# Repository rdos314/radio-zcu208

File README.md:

<h3>Source tree</h3>
vivado - Vivado Verilog source<br>
vitis - Vitis platform and control software<br>
linux - Peta-linux source<br>

<h3>PetaLinux build</h3>
Ubuntu 22.04.5 must be used to build PetaLinux. Link: https://releases.ubuntu.com/jammy/<br><br>

Create a user "ubuntu" since full paths are used in the source.

Install the required software modules before installing PetaLinux:<br>
sudo apt-get install iproute2 gawk python3 python build-essential gcc git make net-tools libncurses5-dev tftpd zlib1g-dev libssl-dev flex bison libselinux1 gnupg wget git-core diffstat chrpath socat xterm autoconf libtool tar unzip texinfo<br><br>

The PetaLinux installer can be downloaded here: https://www.xilinx.com/support/download/index.html/content/xilinx/en/downloadNav/embedded-design-tools.html<br>
Download the "PetaLinux installer" and the "ZCU208 BSP" to /home/ubuntu<br><br>

Install PetaLinux like this:<br>
chmod 755 ./petalinux-v2025.1-final-installer.run<br>
./petalinux-v2025.1-final-installer.run --dir /home/ubuntu/petalinux --platform "arm aarch64"<br>

Source PetaLinux before running commands:<br>
source /home/ubuntu/petalinux/settings.sh<br><br>

Create the project:<br>
mkdir radio-zcu208<br>
cd radio-zcu208<br><br>

petalinux-create -t project -s zcu208-v2025.1.bsp -n linux<br>
cd linux<br><br>

petalinux-config --get-hw-description ../platform/export/platform/hw/sdt<br><br>

Subsystem Hardware Settings -→ Memory settings -→ Set Memory size to 0x70000000<br>
Subsystem Hardware Settings -→ Ethernet settings -→ Disable obtain IP address automatically<br>
Subsystem Hardware Settings -→ Ethernet settings -→ Set Static IP address to 192.168.1.90<br>
Subsystem Hardware Settings -→ Ethernet settings -→ Set Static IP gateway to 192.168.1.1<br>
Image Packaging Configuration  -→  Set Root file system type to EXT4 (SD/eMMC/SATA/USB)<br>

Exit menuconfig and save configuration settings.<br><br>

petalinux-config -c rootfs.<br>

Filesystem Packages -→ console -→ network -→ OpenSSH -→ set openssh-sftp-server to enabled<br>
Filesystem Packages -→ misc -→ set tcf-agent to enabled<br>
Filesystem Packages -→ misc -→ set apache2 to enabled<br><br>

Exit menuconfig and save configuration settings.<br><br>

petalinux-build<br>
petalinux-package boot --uboot --force<br>
petalinux-build --sdk<br>
petalinux-package sysroot<br><br>

Copy linux/images/linux/b31.bin to project roo<br>
Copy linux/images/linux/system.dtb to project root<br>
Copy linux/images/linux/u-boot.elf to project root<br>
Copy linux/images/linux/sdk/sysroots/cortexa72-cotexa53-amd-linux/usr/include to project platform/usr/include<br>
Copy linux/images/linux/sdk/sysroots/cortexa72-cotexa53-amd-linux/usr/lib to project platform/usr/lib<br><br>

cp linux/images/linux/image.ub /media/ubuntu/boot<br>
cp linux/images/linux/boot.scr /media/ubuntu/boot<br>
sudo dd if=linux/images/linux/rootfs.ext4 of=/dev/sdb2<br><br>

<h3>Embedded Vitis</h3>

Embedded Vitis and Vivado can be installed either on Windows or on Linux. Link: https://www.xilinx.com/support/download/index.html/content/xilinx/en/downloadNav/vitis.html<br><br>

For Linux, download and install to /home/user/xilinx and then install the libs like this:<br>
cd /home/user/xilinx/2025.1/Vitis/scripts<br>
sudo ./installLibs.sh<br><br>

<h3>XRT and ZOCL</h3>

https://adaptivesupport.amd.com/s/article/1138667?language=en_US

<h3>Antennas and preamplifiers</h3>

Isolator: https://www.herostechnology.co.uk/pages/RF_Galvanic_Isolators.html                            3 MHz - 2.5 GHz<br>
LNA: https://www.pasternack.com/1.5-db-1.3-ghz-low-noise-amplifier-35-db-gain-sma-pe15a1054-p.aspx      10MHz - 1.3GHz, 35dB, 1.5 NF<br>
LNA: https://www.pasternack.com/1.7-db-550-mhz-low-noise-amplifier-29.7-db-gain-sma-pe15a1044-p.aspx    10MHz - 550 MHz, 30dB, 1.7 NF<br><br>

<h3>Example design</h3>

doc: https://docs.amd.com/r/en-US/ug1309-rf-data-converter-interface<br>
source: https://account.amd.com/en/forms/downloads/design-license-xef.html?filename=RF_Analyzer_2024_2.zip<br><br>

doc: https://www.xilinx.com/publications/products/board-kits/zcu208-dds-ila-2020p2.pdf<br>
source: https://account.amd.com/en/forms/downloads/design-license-xef.html?filename=ZCU208_dds_ila_2020p2.zip<br>

<h3>Important links</h3>
https://www.amd.com/en/products/adaptive-socs-and-fpgas/evaluation-boards/zcu208.html<br>
https://xilinx-wiki.atlassian.net/wiki/spaces/A/pages/18841823/Booting+via+Serial+ATA+SATA+on+ZCU102+Evaluation+Platform<br>
https://adaptivesupport.amd.com/s/article/000037805?language=en_US<br>
https://xilinx-wiki.atlassian.net/wiki/spaces/A/pages/18842475/PetaLinux+Yocto+Tips#PetaLinuxYoctoTips-HowtoAutoRunApplicationatStartup<br>
https://docs.amd.com/r/en-US/Vitis-Tutorials-Embedded-Software<br>
https://docs.amd.com/r/en-US/ug1209-embedded-design-tutorial/Tutorial-Design-Files<br>
https://numato.com/kb/styx-partitioning-sd-card-for-petalinux/<br>
https://adaptivesupport.amd.com/s/article/1192842?language=en_US<br>
https://github.com/Xilinx/embeddedsw/blob/master/XilinxProcessorIPLib/drivers/rfdc/examples/xrfdc_mts_example.c<br>
https://docs.amd.com/r/en-US/pg269-rf-data-converter/MTS-Sequencing<br>
https://docs.amd.com/r/en-US/ug835-vivado-tcl-commands/<br>
https://github.com/Xilinx/embeddedsw/tree/master/XilinxProcessorIPLib/drivers/board_common/src/rfclk<br>
https://layers.openembedded.org/layerindex/branch/master/layers/<br>
https://www.analog.com/en/products/adl5569.html<br>
https://ez.analog.com/rf/f/q-a/115814/adl5569-single-ended-input<br>

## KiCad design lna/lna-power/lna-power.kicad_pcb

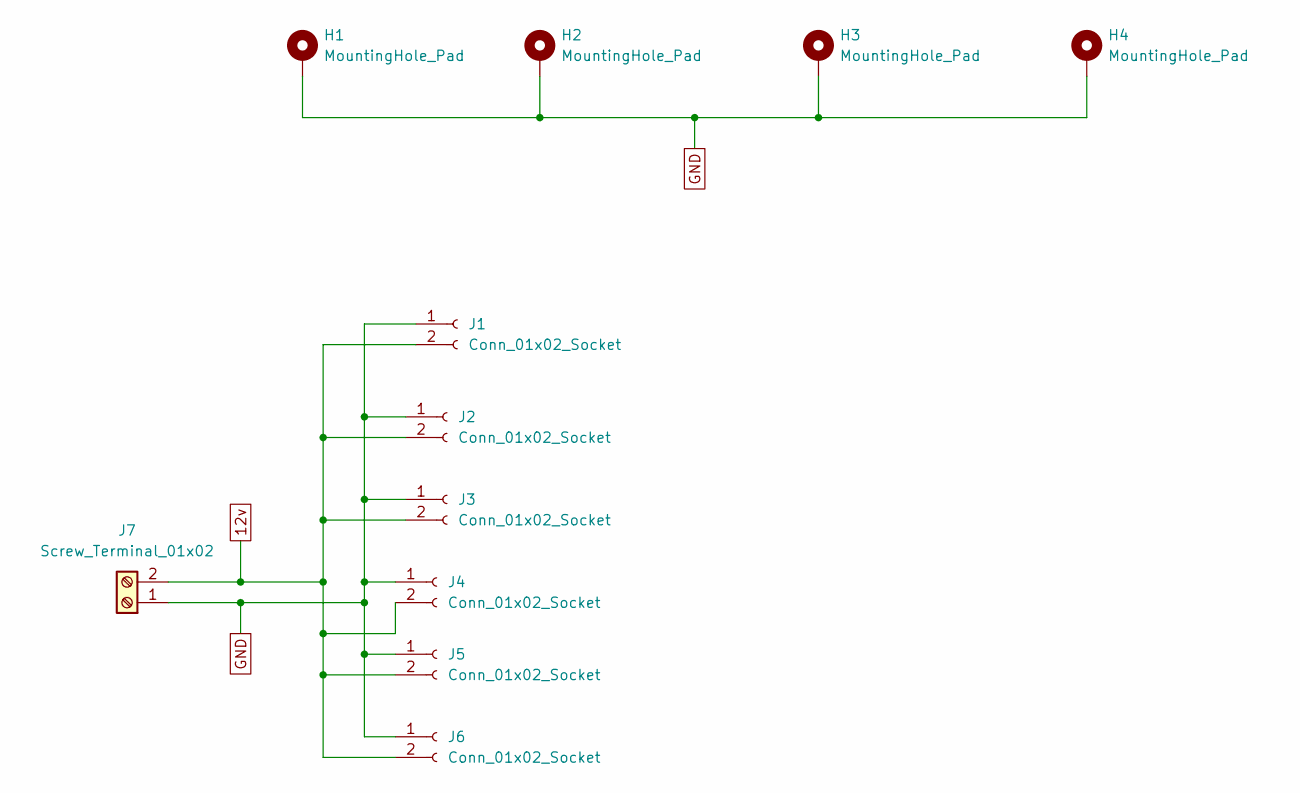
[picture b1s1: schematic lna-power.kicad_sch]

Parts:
H1, H2, H3, H4: MountingHole_Pad; MountingHole_4.3mm_M4_Pad_Via
J1, J2, J3, J4, J5, J6: Conn_01x02_Socket; PinHeader_1x02_P2.54mm_Vertical
J7: Screw_Terminal_01x02; TerminalBlock_Phoenix_MKDS-1,5-2_1x02_P5.00mm_Horizontal

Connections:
12v: J1.2, J2.2, J3.2, J4.2, J5.2, J6.2, J7.2
GND: H1.1 (1_1), H2.1 (1_1), H3.1 (1_1), H4.1 (1_1), J1.1, J2.1, J3.1, J4.1, J5.1, J6.1, J7.1

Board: 2 copper layers, 11 parts (6 on the bottom side), 2 nets, no tracks yet.

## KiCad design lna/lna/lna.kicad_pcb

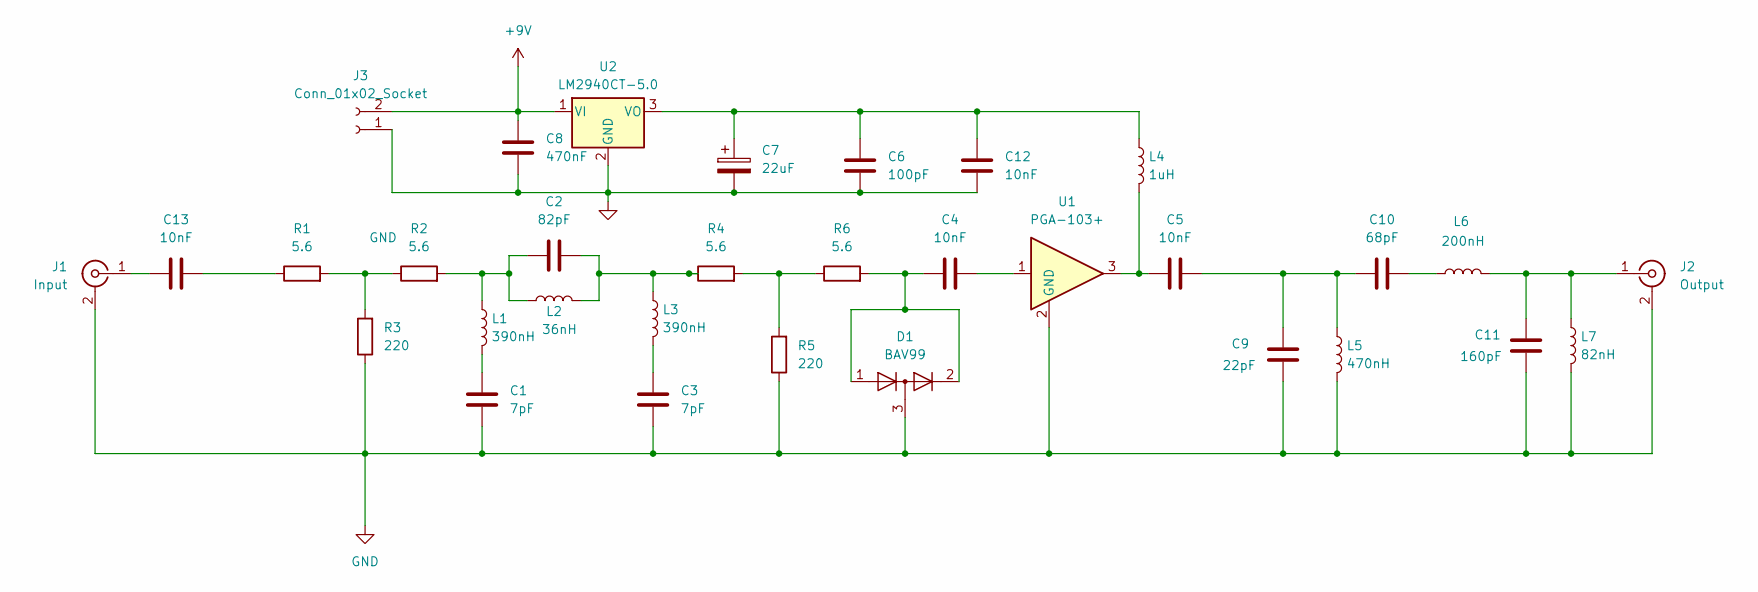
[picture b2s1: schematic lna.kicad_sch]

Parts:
C1, C3: 7pF; C_0402_1005Metric_Pad0.74x0.62mm_HandSolder
C2: 82pF; C_0402_1005Metric_Pad0.74x0.62mm_HandSolder
C4, C5, C13: 10nF; C_0402_1005Metric_Pad0.74x0.62mm_HandSolder
C6: 100pF; C_0805_2012Metric_Pad1.18x1.45mm_HandSolder
C7: 22uF; CP_Radial_D6.3mm_P2.50mm
C8: 470nF; C_Radial_D10.0mm_H12.5mm_P5.00mm
C9: 22pF; C_0402_1005Metric_Pad0.74x0.62mm_HandSolder
C10: 68pF; C_0402_1005Metric_Pad0.74x0.62mm_HandSolder
C11: 160pF; C_0402_1005Metric_Pad0.74x0.62mm_HandSolder
C12: 10nF; C_0805_2012Metric_Pad1.18x1.45mm_HandSolder
D1: BAV99; SOT-23
J1: Input; SMA_Amphenol_132289_EdgeMount
J2: Output; SMA_Amphenol_132289_EdgeMount
J3: Conn_01x02_Socket; PinSocket_1x02_P2.54mm_Horizontal
L1, L3: 390nH; L_0402_1005Metric_Pad0.77x0.64mm_HandSolder
L2: 36nH; L_0402_1005Metric_Pad0.77x0.64mm_HandSolder
L4: 1uH; L_0805_2012Metric_Pad1.05x1.20mm_HandSolder
L5: 470nH; L_0402_1005Metric_Pad0.77x0.64mm_HandSolder
L6: 200nH; L_0402_1005Metric_Pad0.77x0.64mm_HandSolder
L7: 82nH; L_0402_1005Metric_Pad0.77x0.64mm_HandSolder
R1, R2, R4, R6: 5.6; R_0402_1005Metric_Pad0.72x0.64mm_HandSolder
R3, R5: 220; R_0402_1005Metric_Pad0.72x0.64mm_HandSolder
U1: PGA-103+; SOT-89-3_Handsoldering
U2: LM2940CT-5.0; TO-220-3_Horizontal_TabDown

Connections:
+9V: C8.1, J3.2, U2.1 (VI)
GND: C1.2, C3.2, C6.2, C7.2, C8.2, C9.2, C11.2, C12.2, D1.3 (K), J1.2 (Ext), J2.2 (Ext), J3.1, L5.2, L7.2, R3.1, R5.1, U1.2 (GND_2), U2.2 (GND)
unnamed: C1.1, L1.2
unnamed: C2.1, L1.1, L2.1, R2.2
unnamed: C2.2, L2.2, L3.1, R4.1
unnamed: C3.1, L3.2
unnamed: C4.2, U1.1
unnamed: C5.1, L4.2, U1.3
unnamed: C5.2, C9.1, C10.1, L5.1
unnamed: C10.2, L6.1
unnamed: C13.2, R1.1
unnamed: C4.1, D1.1 (K), D1.2 (A), R6.2
unnamed: C13.1, J1.1 (In)
unnamed: C11.1, J2.1 (In), L6.2, L7.1
unnamed: R1.2, R2.1, R3.2
unnamed: R4.2, R5.2, R6.1
unnamed: C6.1, C7.1, C12.1, L4.1, U2.3 (VO)

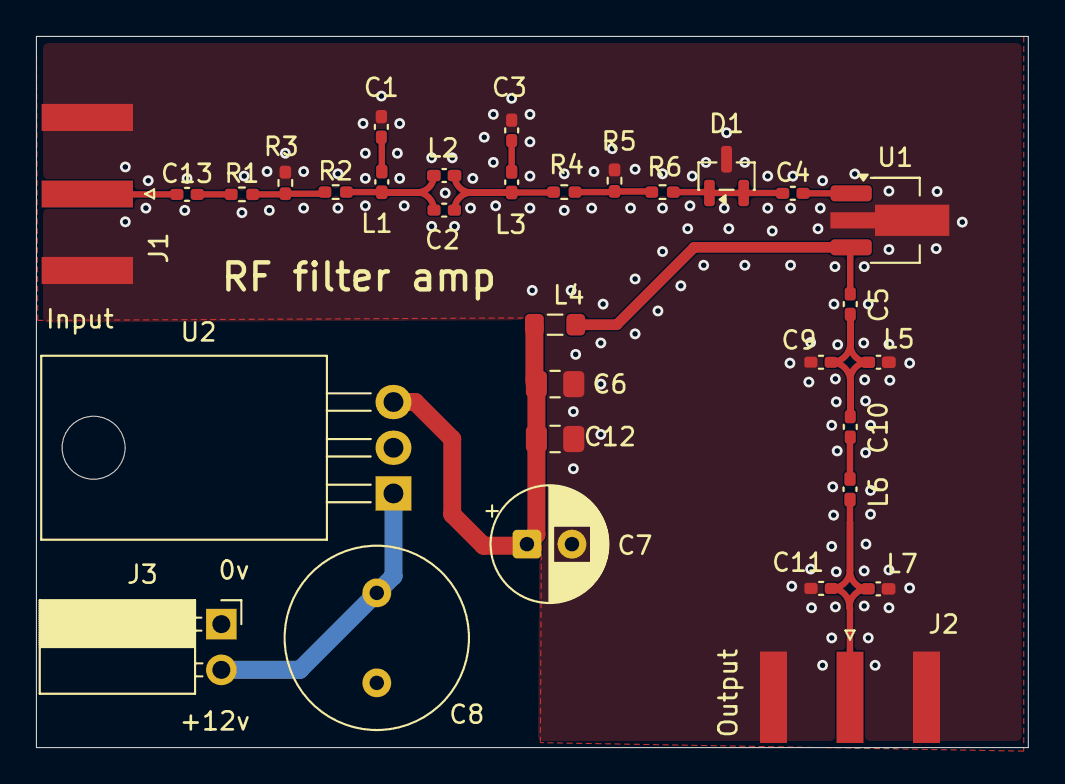
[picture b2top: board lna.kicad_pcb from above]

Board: 4 copper layers, 55.1 x 39.5 mm, 32 parts (0 on the bottom side), 17 nets.

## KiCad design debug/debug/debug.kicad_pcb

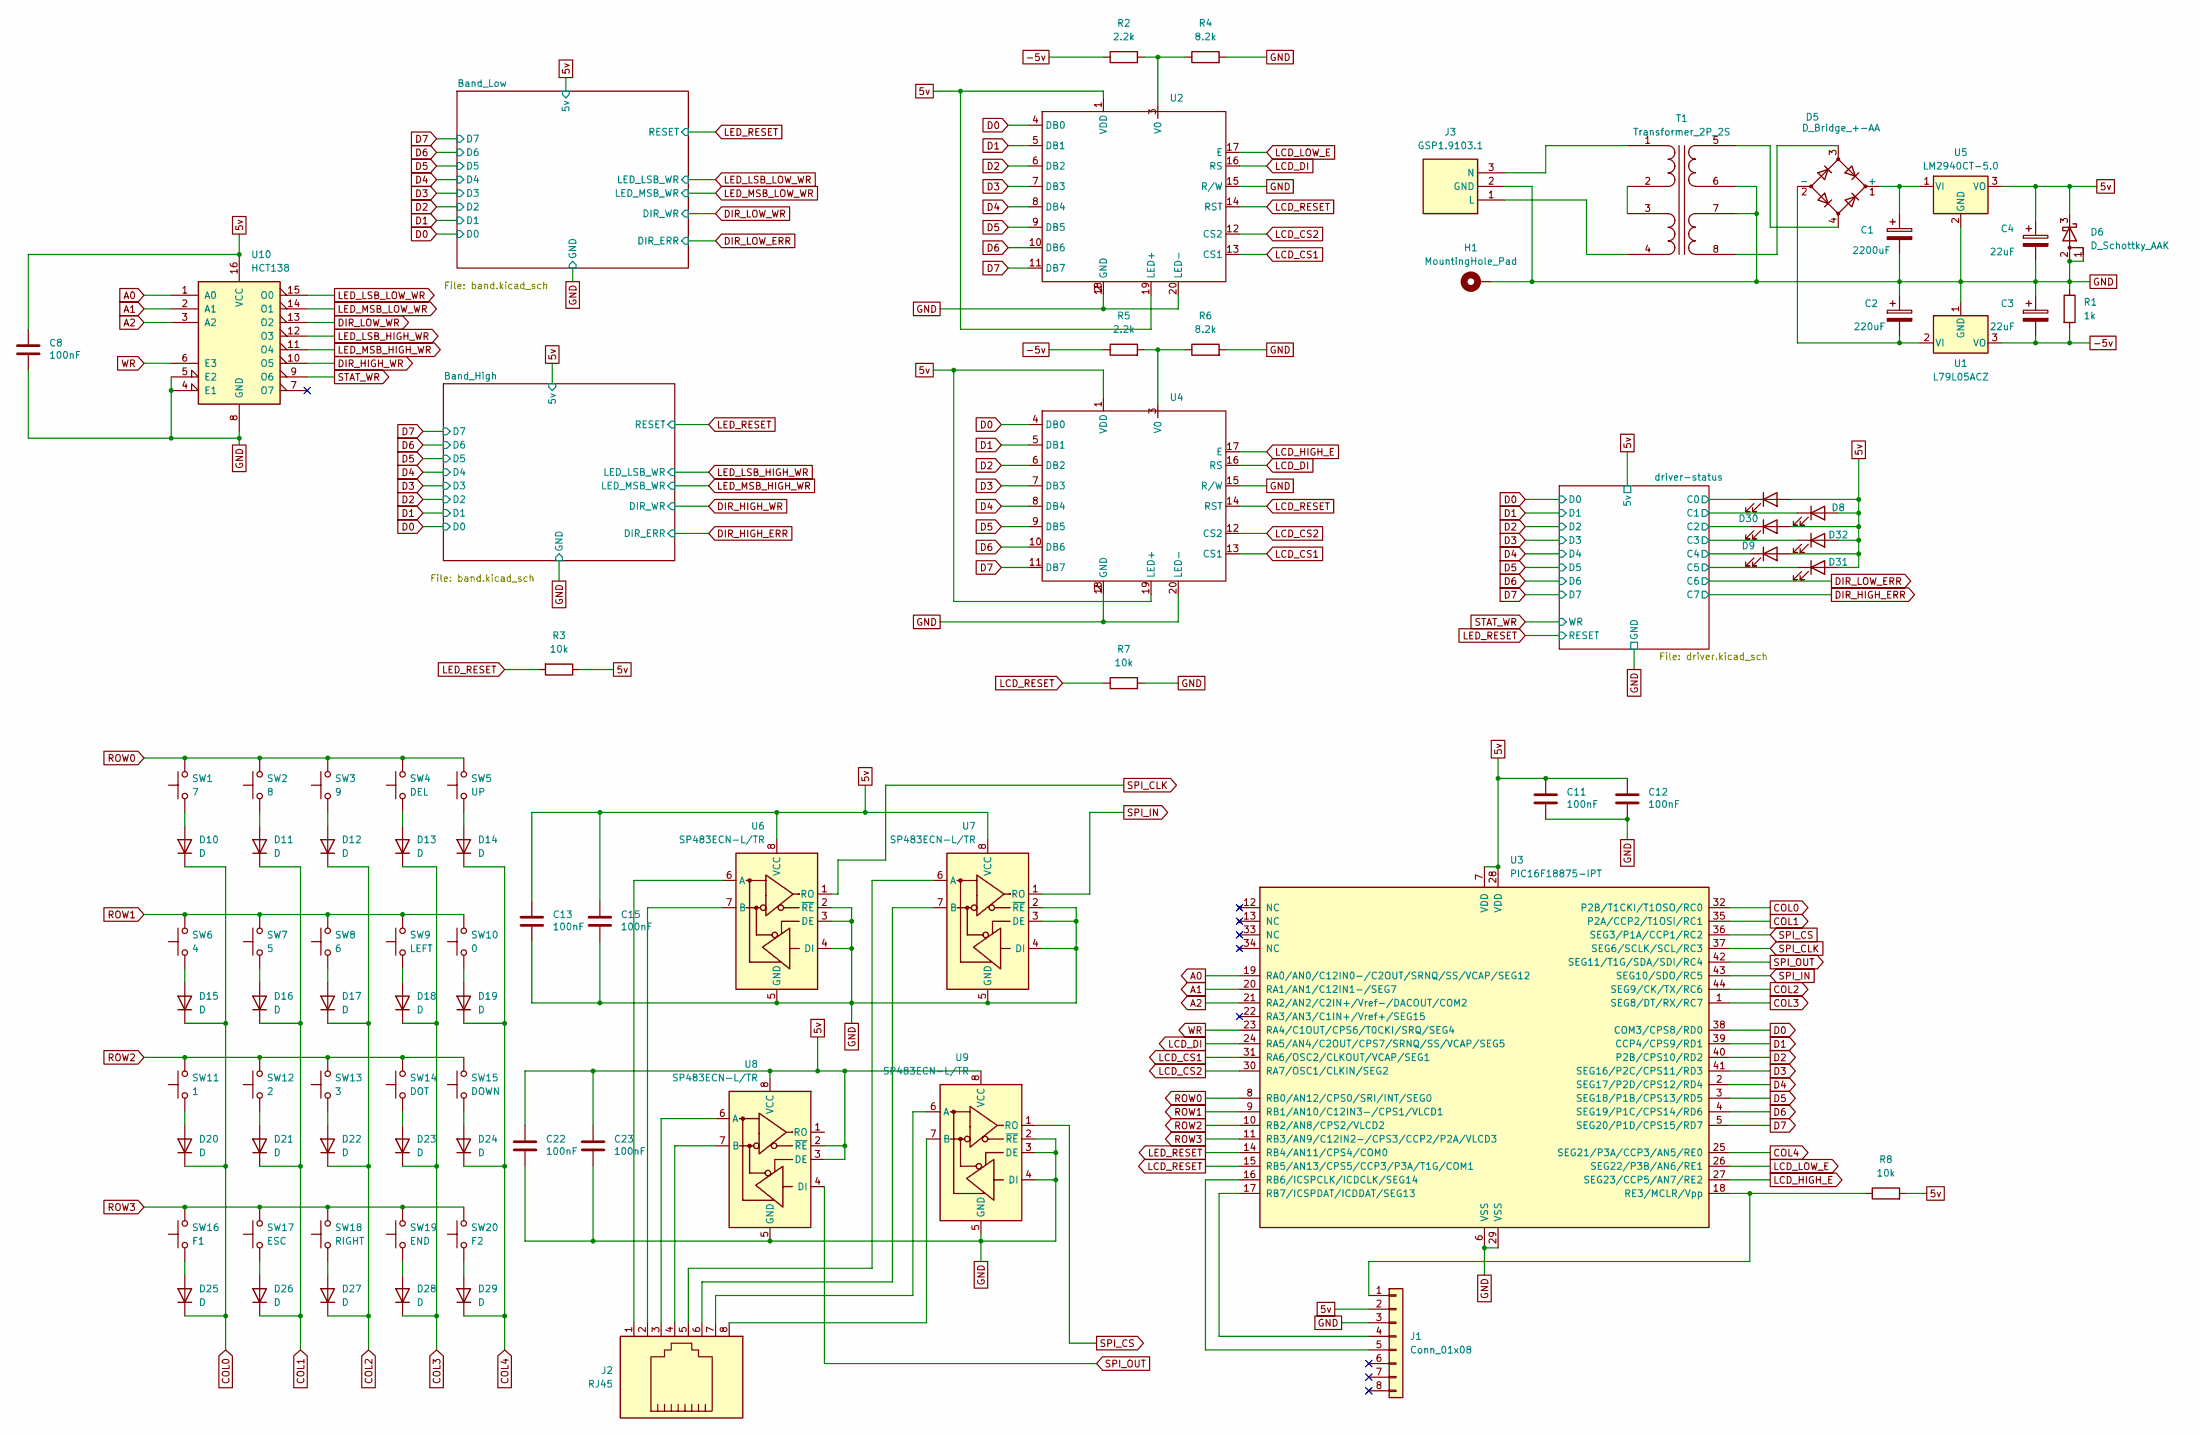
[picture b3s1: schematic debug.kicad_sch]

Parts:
C1: 2200uF; CP_Radial_D10.0mm_P5.00mm
C2: 220uF; CP_Radial_D6.3mm_P2.50mm
C3, C4: 22uF; CP_Radial_D6.3mm_P2.50mm
C8, C11, C12, C13, C15, C22, C23: 100nF; C_0805_2012Metric_Pad1.18x1.45mm_HandSolder
D5: D_Bridge_+-AA; Diode_Bridge_DIP-4_W7.62mm_P5.08mm
D6: D_Schottky_AAK; SOT-23
D7: LED_ON_LOW; LED_D5.0mm
D8: LED_ON_HIGH; LED_D5.0mm
D9: LED_PIC; LED_D5.0mm
D10, D11, D12, D13, D14, D15, D16, D17, D18, D19, D20, D21, D22, D23, D24, D25, D26, D27, D28, D29: D; D_SOD-123
D30: LED_AUX1; LED_D5.0mm
D31: LED_FPGA; LED_D5.0mm
D32: LED_AUX2; LED_D5.0mm
H1: MountingHole_Pad; MountingHole_4.3mm_M4_Pad_Via
J1: Conn_01x08; PinHeader_1x08_P2.54mm_Vertical
J2: RJ45; E5J8800LJG2L
J3: GSP1.9103.1; GSP191031; Manufacturer_Part_Number GSP1.9103.1; Mouser Part Number 693-GSP1.9103.1
R1: 1k; R_0805_2012Metric_Pad1.20x1.40mm_HandSolder
R2, R5: 2.2k; R_0805_2012Metric_Pad1.20x1.40mm_HandSolder
R3, R7, R8: 10k; R_0805_2012Metric_Pad1.20x1.40mm_HandSolder
R4, R6: 8.2k; R_0805_2012Metric_Pad1.20x1.40mm_HandSolder
SW1: 7; SW_Cherry_MX_1.00u_PCB
SW2: 8; SW_Cherry_MX_1.00u_PCB
SW3: 9; SW_Cherry_MX_1.00u_PCB
SW4: DEL; SW_Cherry_MX_1.00u_PCB
SW5: UP; SW_Cherry_MX_1.00u_PCB
SW6: 4; SW_Cherry_MX_1.00u_PCB
SW7: 5; SW_Cherry_MX_1.00u_PCB
SW8: 6; SW_Cherry_MX_1.00u_PCB
SW9: LEFT; SW_Cherry_MX_1.00u_PCB
SW10: 0; SW_Cherry_MX_1.00u_PCB
SW11: 1; SW_Cherry_MX_1.00u_PCB
SW12: 2; SW_Cherry_MX_1.00u_PCB
SW13: 3; SW_Cherry_MX_1.00u_PCB
SW14: DOT; SW_Cherry_MX_1.00u_PCB
SW15: DOWN; SW_Cherry_MX_1.00u_PCB
SW16: F1; SW_Cherry_MX_1.00u_PCB
SW17: ESC; SW_Cherry_MX_1.00u_PCB
SW18: RIGHT; SW_Cherry_MX_1.00u_PCB
SW19: END; SW_Cherry_MX_1.00u_PCB
SW20: F2; SW_Cherry_MX_1.00u_PCB
T1: Transformer_2P_2S; FP16-1500
U1: L79L05ACZ; TO-92_Inline_Wide
U2, U4: LCD
U3: PIC16F18875-IPT; TQFP-44_10x10mm_P0.8mm
U5: LM2940CT-5.0; TO-220-3_Horizontal_TabUp
U6, U7, U8, U9: SP483ECN-L/TR; SOIC-8_3.9x4.9mm_P1.27mm
U10: HCT138; SOIC-16_3.9x9.9mm_P1.27mm

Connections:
5v: C4.1, C8.1, C11.1, C12.1, C13.1, C15.1, C22.1, C23.1, D6.3 (K), D7.2 (A), D8.2 (A), D9.2 (A), D30.2 (A), D31.2 (A), D32.2 (A), J1.2, R3.1, R8.2, U2.1 (VDD), U2.19 (LED+), U3.7 (VDD), U3.28 (VDD), U4.1 (VDD), U4.19 (LED+), U5.3 (VO), U6.8 (VCC), U7.8 (VCC), U8.2 (~RE), U8.3 (DE), U8.8 (VCC), U9.8 (VCC), U10.16 (VCC); also elsewhere on the board
-5v: C3.2, R1.2, R2.1, R5.1, U1.3 (VO)
/driver-status/C0: D7.1 (K); also elsewhere on the board
/driver-status/C1: D8.1 (K); also elsewhere on the board
/driver-status/C2: D30.1 (K); also elsewhere on the board
/driver-status/C3: D32.1 (K); also elsewhere on the board
/driver-status/C4: D9.1 (K); also elsewhere on the board
/driver-status/C5: D31.1 (K); also elsewhere on the board
A0: U3.19 (RA0/AN0/C12IN0-/C2OUT/SRNQ/SS/VCAP/SEG12), U10.1 (A0)
A1: U3.20 (RA1/AN1/C12IN1-/SEG7), U10.2 (A1)
A2: U3.21 (RA2/AN2/C2IN+/Vref-/DACOUT/COM2), U10.3 (A2)
COL0: D10.1 (K), D15.1 (K), D20.1 (K), D25.1 (K), U3.32 (P2B/T1CKI/T1OSO/RC0)
COL1: D11.1 (K), D16.1 (K), D21.1 (K), D26.1 (K), U3.35 (P2A/CCP2/T1OSI/RC1)
COL2: D12.1 (K), D17.1 (K), D22.1 (K), D27.1 (K), U3.44 (SEG9/CK/TX/RC6)
COL3: D13.1 (K), D18.1 (K), D23.1 (K), D28.1 (K), U3.1 (SEG8/DT/RX/RC7)
COL4: D14.1 (K), D19.1 (K), D24.1 (K), D29.1 (K), U3.25 (SEG21/P3A/CCP3/AN5/RE0)
D0: U2.4 (DB0), U3.38 (COM3/CPS8/RD0), U4.4 (DB0); also elsewhere on the board
D1: U2.5 (DB1), U3.39 (CCP4/CPS9/RD1), U4.5 (DB1); also elsewhere on the board
D2: U2.6 (DB2), U3.40 (P2B/CPS10/RD2), U4.6 (DB2); also elsewhere on the board
D3: U2.7 (DB3), U3.41 (SEG16/P2C/CPS11/RD3), U4.7 (DB3); also elsewhere on the board
D4: U2.8 (DB4), U3.2 (SEG17/P2D/CPS12/RD4), U4.8 (DB4); also elsewhere on the board
D5: U2.9 (DB5), U3.3 (SEG18/P1B/CPS13/RD5), U4.9 (DB5); also elsewhere on the board
D6: U2.10 (DB6), U3.4 (SEG19/P1C/CPS14/RD6), U4.10 (DB6); also elsewhere on the board
D7: U2.11 (DB7), U3.5 (SEG20/P1D/CPS15/RD7), U4.11 (DB7); also elsewhere on the board
DIR_HIGH_WR: U10.10 (O5); also elsewhere on the board
DIR_LOW_WR: U10.13 (O2); also elsewhere on the board
GND: C1.2, C2.1, C3.1, C4.2, C8.2, C11.2, C12.2, C13.2, C15.2, C22.2, C23.2, D6.1 (A), D6.2 (A), H1.1 (1_1), J1.3, J3.2 (GND), R1.1, R4.2, R6.2, R7.2, T1.6 (OUT1B), T1.7 (OUT2A), U1.1 (GND), U2.2 (GND), U2.15 (R/W), U2.18 (GND), U2.20 (LED-), U3.6 (VSS), U3.29 (VSS), U4.2 (GND), U4.15 (R/W), U4.18 (GND), U4.20 (LED-), U5.2 (GND), U6.2 (~RE), U6.3 (DE), U6.4 (DI), U6.5 (GND), U7.2 (~RE), U7.3 (DE), U7.4 (DI), U7.5 (GND), U8.5 (GND), U9.2 (~RE), U9.3 (DE), U9.4 (DI), U9.5 (GND), U10.4 (E1), U10.5 (E2), U10.8 (GND); also elsewhere on the board
LCD_CS1: U2.13 (CS1), U3.31 (RA6/OSC2/CLKOUT/VCAP/SEG1), U4.13 (CS1)
LCD_CS2: U2.12 (CS2), U3.30 (RA7/OSC1/CLKIN/SEG2), U4.12 (CS2)
LCD_DI: U2.16 (RS), U3.24 (RA5/AN4/C2OUT/CPS7/SRNQ/SS/VCAP/SEG5), U4.16 (RS)
LCD_HIGH_E: U3.27 (SEG23/CCP5/AN7/RE2), U4.17 (E)
LCD_LOW_E: U2.17 (E), U3.26 (SEG22/P3B/AN6/RE1)
LCD_RESET: R7.1, U2.14 (RST), U3.15 (RB5/AN13/CPS5/CCP3/P3A/T1G/COM1), U4.14 (RST)
LED_LSB_HIGH_WR: U10.12 (O3); also elsewhere on the board
LED_LSB_LOW_WR: U10.15 (O0); also elsewhere on the board
LED_MSB_HIGH_WR: U10.11 (O4); also elsewhere on the board
LED_MSB_LOW_WR: U10.14 (O1); also elsewhere on the board
LED_RESET: R3.2, U3.14 (RB4/AN11/CPS4/COM0); also elsewhere on the board
unnamed: C1.1, D5.1 (+), U5.1 (VI)
unnamed: C2.2, D5.2 (-), U1.2 (VI)
unnamed: D10.2 (A), SW1.1
unnamed: D11.2 (A), SW2.1
unnamed: D12.2 (A), SW3.1
unnamed: D13.2 (A), SW4.1
unnamed: D14.2 (A), SW5.1
unnamed: D15.2 (A), SW6.1
unnamed: D16.2 (A), SW7.1
unnamed: D17.2 (A), SW8.1
unnamed: D18.2 (A), SW9.1
unnamed: D19.2 (A), SW10.1
unnamed: D20.2 (A), SW11.1
unnamed: D21.2 (A), SW12.1
unnamed: D22.2 (A), SW13.1
unnamed: D23.2 (A), SW14.1
unnamed: D24.2 (A), SW15.1
unnamed: D25.2 (A), SW16.1
unnamed: D26.2 (A), SW17.1
unnamed: D27.2 (A), SW18.1
unnamed: D28.2 (A), SW19.1
unnamed: D29.2 (A), SW20.1
unnamed: J1.1, R8.1, U3.18 (RE3/MCLR/Vpp)
unnamed: J1.4, U3.17 (RB7/ICSPDAT/ICDDAT/SEG13)
unnamed: J1.5, U3.16 (RB6/ICSPCLK/ICDCLK/SEG14)
unnamed: J3.1 (L), T1.4 (IN2B)
unnamed: J3.3 (N), T1.1 (IN1A)
unnamed: T1.2 (IN1B), T1.3 (IN2A)
unnamed: D5.4, T1.5 (OUT1A)
unnamed: D5.3, T1.8 (OUT2B)
unnamed: R2.2, R4.1, U2.3 (V0)
unnamed: R5.2, R6.1, U4.3 (V0)
unnamed: J2.1, U6.6 (A)
unnamed: J2.2, U6.7 (B)
unnamed: J2.5, U7.6 (A)
unnamed: J2.6, U7.7 (B)
unnamed: J2.3, U8.6 (A)
unnamed: J2.4, U8.7 (B)
unnamed: J2.7, U9.6 (A)
unnamed: J2.8, U9.7 (B)
ROW0: SW1.2, SW2.2, SW3.2, SW4.2, SW5.2, U3.8 (RB0/AN12/CPS0/SRI/INT/SEG0)
ROW1: SW6.2, SW7.2, SW8.2, SW9.2, SW10.2, U3.9 (RB1/AN10/C12IN3-/CPS1/VLCD1)
ROW2: SW11.2, SW12.2, SW13.2, SW14.2, SW15.2, U3.10 (RB2/AN8/CPS2/VLCD2)
ROW3: SW16.2, SW17.2, SW18.2, SW19.2, SW20.2, U3.11 (RB3/AN9/C12IN2-/CPS3/CCP2/P2A/VLCD3)
SPI_CLK: U3.37 (SEG6/SCLK/SCL/RC3), U6.1 (RO)
SPI_CS: U3.36 (SEG3/P1A/CCP1/RC2), U9.1 (RO)
SPI_IN: U3.43 (SEG10/SDO/RC5), U7.1 (RO)
SPI_OUT: U3.42 (SEG11/T1G/SDA/SDI/RC4), U8.4 (DI)
STAT_WR: U10.9 (O6); also elsewhere on the board
WR: U3.23 (RA4/C1OUT/CPS6/T0CKI/SRQ/SEG4), U10.6 (E3)
